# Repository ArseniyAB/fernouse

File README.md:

# fernouse
Gaming mice kinda suck... This one shouldn't. 

## Features
* 1000Hz+ polling rate - If I don't hit 1k, I did something wrong.
* Wireless and Wired USB-C connection
* 13 buttons
    * left-right tilt mouse wheel buttons
    * 4 thumb buttons + 5th button on thumb rest
    * 2 buttons to the side of the left-primary button
    * 1 button behind scroll wheel
    * 1 button on scroll wheel
* Magnetic-sense scroll wheel
* 400mAh battery for ~10h operation (TBD)
* Weight: As close to 100g as I can get it (TBD)
* Extra buttons Mapped to keyboard characters (cuz some games still have    trouble with extra mouse buttons)

## Critical Hardware
* Main Chip on mouse: nRF52840
* Main buttons:  Omron D2FC-F-7N(60M)
* Auxilary buttons: omron D3C-1220
* Sensor: PAW3395 
* Mangetic Sensor: TMAG6180 (analog sine/cosine)
* USB-C connector
* Dongle: NRF52840 MDK USB DONGLE (literally easiest decision of my life)
    ### For maximum polling rate
    * Change dongle to a STM32H753ZI Nucleo-144 STM32H7 ARM® Cortex®-M7 MCU 32-Bit Embedded Evaluation Board
        for faster USB polling speeds (STM32 supports HighSpeed USB)
    * Attach the original NRF52 dongle to the STM as a simple receiver
* Small magnet to place inside of the mouse wheel

## Signal Filtering
* It would make sense to at least leave space for a low pass filter for the sinusoidal outputs of the magnetic field sensor. 
    This may even be required for the same reason mentioned in the next point, we're already doing ArcTan calcs 

* Debounce all buttons with a small cap <- Hoping not to have to debounce in software increasing delay

*

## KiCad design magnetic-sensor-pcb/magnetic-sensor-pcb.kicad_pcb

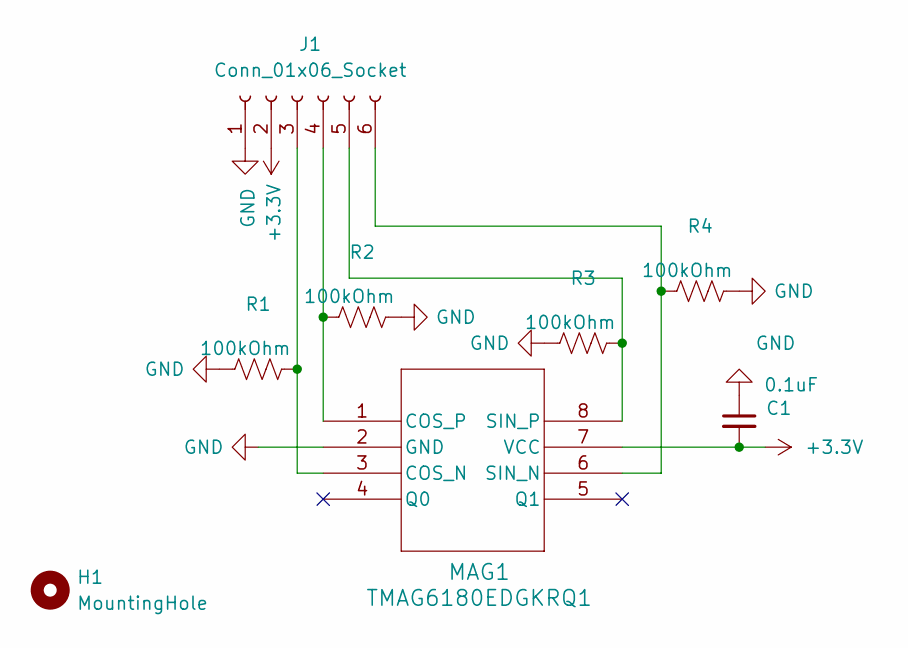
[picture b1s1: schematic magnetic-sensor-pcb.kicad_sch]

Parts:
C1: C_Small; C_0402_1005Metric
H1: MountingHole; ToolingHole_1.152mm
J1: Conn_01x06_Socket; PinHeader_1x06_P1.00mm_Horizontal
MAG1: TMAG6180EDGKRQ1; VSSOP8_3P1X3P1_TEX
R1, R2, R3, R4: R_US; R_0402_1005Metric

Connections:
+3.3V: C1.2, J1.2, MAG1.7 (VCC)
GND: C1.1, J1.1, MAG1.2 (GND), R1.1, R2.2, R3.1, R4.2
unnamed: J1.3, MAG1.3 (COS_N), R1.2
unnamed: J1.4, MAG1.1 (COS_P), R2.1
unnamed: J1.5, MAG1.8 (SIN_P), R3.2
unnamed: J1.6, MAG1.6 (SIN_N), R4.1

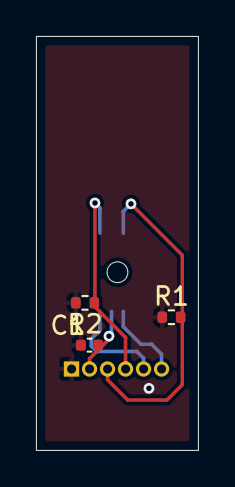
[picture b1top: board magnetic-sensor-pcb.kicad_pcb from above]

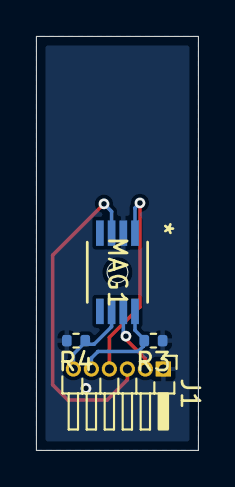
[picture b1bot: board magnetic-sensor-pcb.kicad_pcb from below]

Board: 2 copper layers, 9.0 x 23.0 mm, 8 parts (4 on the bottom side), 6 nets.

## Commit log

2026-02-15 making footprints and starting pcb work
2026-02-15 updating readme
2026-02-15 changing indents
2026-02-15 realized the magnetic sensor wont work because of orientation
2026-02-15 adding secondary pcb for magnetic field sensor
2026-02-15 more thoughts in the readme
